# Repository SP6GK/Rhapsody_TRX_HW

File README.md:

# Rhapsody Project

Rhapsody is an ongoing project focused on the development of a modular amateur radio transceiver. The current version of the project features the zero-IF board, which utilizes two balanced Tayloe mixers to convert 1-30 MHz RF signals into baseband IQ that can be processed by an ADC, and to convert baseband IQ generated by a DAC into output RF, implementing a simplex HF transceiver.

In this repository, you can find the first module developed for the Rhapsody project - the IQ board. This PCB implements two balanced Tayloe mixers (or product detectors if you prefer) to implement both transmit and receive paths for an SDR transceiver. Together with a microcontroller and ADC+DAC (or a PC with a sound card), you can create a working HF software-defined transceiver. Special care was put into the design to provide the best IQ balance for superb opposite sideband attenuation.

I have presented more measurements and theory of operation on my personal website: [Description of Rhapsody project on SP6GK.com](https://www.sp6gk.com/Rhapsody_IQ_Board.html). Bare in mind that these results were possible thanks to low tolerance components in the feedback loops of the op amps and software tuning.

The current version of the IQ board is designed for testability. Zero Ohm resistors are implemented as jumpers so that different configurations of RF transformers can be tested. If the value of a resistor is not provided, it is most likely not to be populated (DNP). On the other hand, the zero-Ohm resistors indicate the default option.
RF transformers were wound on FT37-43.

The above results were obtained with my software running on an STM32F407 with a 24-bit 48 KHz ADC/DAC on the I2S interface. [Link to software repository](https://github.com/SP6GK/Rhapsody_TRX_SW)

**Experimental features include:**
- Option to include an additional active LPF in the IQ signal path before the ADC (better spurious image rejection and better anti-aliasing, but may cause worse IQ imbalance; not tested yet)
- Additional passive RC LPF before the RX op amps
- 2.5V reference created by impedance buffer - higher current output for the 2.5V rail should provide even better stability
- External oscillator can be used with a single-ended input. A Johnson Counter then creates an IQ LO. This solution limits the operating frequency to 1/4 of the maximum frequency of the 74xx74 chip used. The onboard PLL can provide an LO signal up to 100 MHz, and its reference is a TCXO or a simple crystal.

**How does it work?**
I recommend the following resources if you want to understand more about the hardware behind this project:
- **Best place to learn about the Tayloe mixer** by Dan Tayloe, [Ultra Low Noise, High Performance, Zero IF Quadrature Product Detector and Preamplifier](https://norcalqrp.org/files/Tayloe_mixer_x3a.pdf)
- **Further description of SDR** by Gerald Youngblood, [A Software-Defined Radio for the Masses](https://www.arrl.org/files/file/Technology/tis/info/pdf/020708qex013.pdf)

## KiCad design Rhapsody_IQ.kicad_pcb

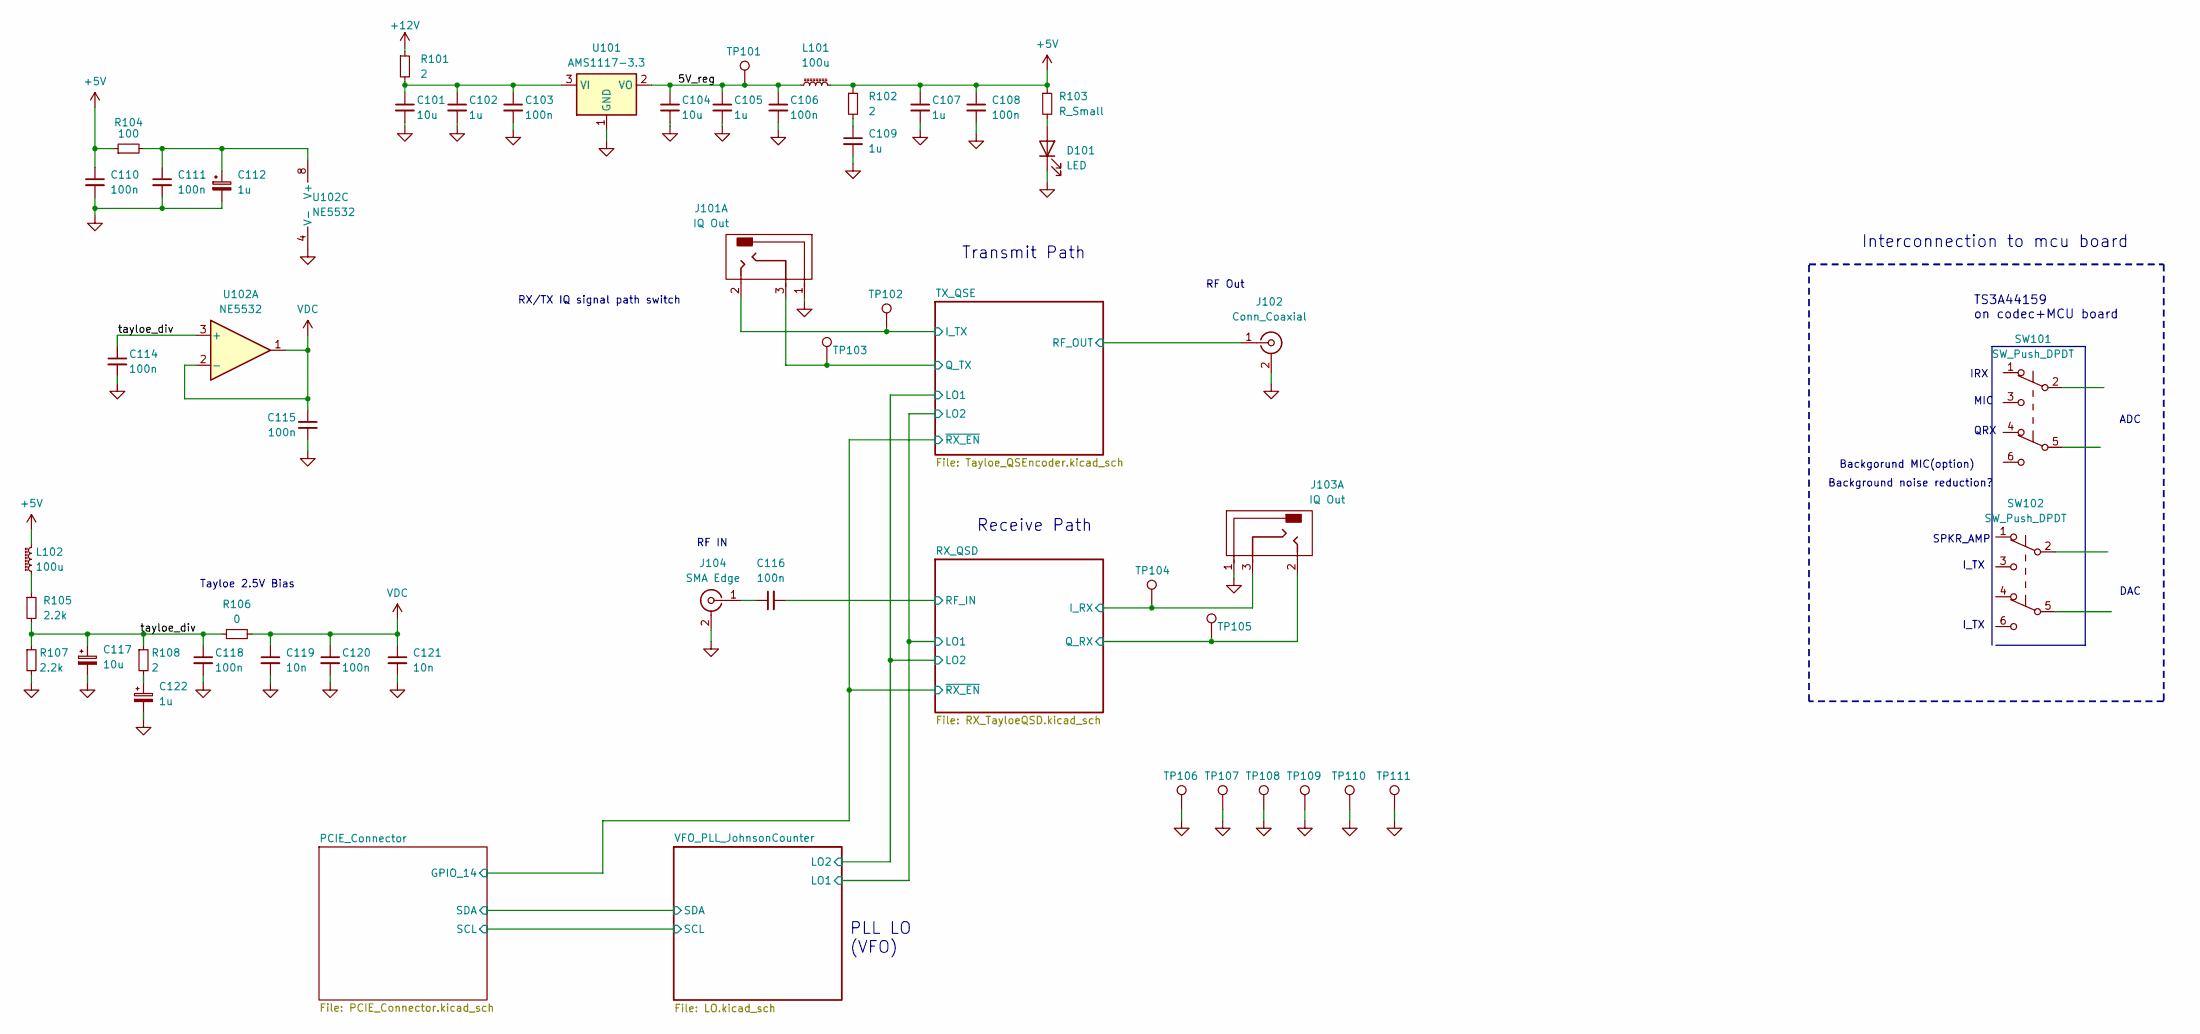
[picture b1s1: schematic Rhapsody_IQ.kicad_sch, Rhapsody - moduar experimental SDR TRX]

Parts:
C101, C104, C117: 10u; C_1206_3216Metric_Pad1.33x1.80mm_HandSolder
C102, C105, C107, C109, C112, C122: 1u; C_0603_1608Metric_Pad1.08x0.95mm_HandSolder
C103, C106, C108, C110, C111, C114, C115, C116, C118, C120: 100n; C_0603_1608Metric_Pad1.08x0.95mm_HandSolder
C119, C121: 10n; C_0603_1608Metric_Pad1.08x0.95mm_HandSolder
D101: LED; D_0805_2012Metric_Pad1.15x1.40mm_HandSolder
J101, J103: IQ Out; Jack_3.5mm_CUI_SJ-3524-SMT_Horizontal
J102: Conn_Coaxial; SMA_Amphenol_132289_EdgeMount
J104: SMA Edge; SMA_Amphenol_132289_EdgeMount
L101, L102: 100u; L_1206_3216Metric_Pad1.22x1.90mm_HandSolder
R101: 2; R_0805_2012Metric_Pad1.20x1.40mm_HandSolder
R102, R108: 2; R_0603_1608Metric_Pad0.98x0.95mm_HandSolder
R103: R_Small; R_0805_2012Metric_Pad1.20x1.40mm_HandSolder
R104: 100; R_0603_1608Metric_Pad0.98x0.95mm_HandSolder
R105, R107: 2.2k; R_0603_1608Metric_Pad0.98x0.95mm_HandSolder
R106: 0; R_0805_2012Metric_Pad1.20x1.40mm_HandSolder
SW101, SW102: SW_Push_DPDT
TP101, TP102, TP103, TP104, TP105, TP106, TP107, TP108, TP109: TestPoint; TestPoint_Pad_D1.5mm
TP110, TP111: TestPoint; TestPoint_Pad_4.0x4.0mm
U101: AMS1117-3.3; SOT-223-3_TabPin2
U102: NE5532; SOIC-8_3.9x4.9mm_P1.27mm

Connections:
+5V: C107.1, C108.1, C110.1, L101.2, L102.2, R102.1, R103.1, R104.1; also elsewhere on the board
+12V: R101.1; also elsewhere on the board
/5V_reg: C104.1, C105.1, C106.1, L101.1, TP101.1, U101.2 (VO)
/RX_QSD/I_RX: J103.3, TP104.1; also elsewhere on the board
/RX_QSD/Q_RX: J103.2, TP105.1; also elsewhere on the board
/RX_QSD/RF_IN: C116.2; also elsewhere on the board
/TX_QSE/I_TX: J101.2, TP102.1; also elsewhere on the board
/TX_QSE/Q_TX: J101.3, TP103.1; also elsewhere on the board
/TX_QSE/RF_OUT: J102.1 (In); also elsewhere on the board
/tayloe_div: C114.1, C117.1, C118.1, R105.2, R106.1, R107.1, R108.1, U102.3 (+)
GND: C101.2, C102.2, C103.2, C104.2, C105.2, C106.2, C107.2, C108.2, C109.2, C110.2, C111.2, C112.2, C114.2, C115.2, C117.2, C118.2, C119.2, C120.2, C121.2, C122.2, D101.1 (K), J101.1, J102.2 (Ext), J103.1, J104.2 (Ext), R107.2, TP106.1, TP107.1, TP108.1, TP109.1, TP110.1, TP111.1, U101.1 (GND), U102.4 (V-); also elsewhere on the board
unnamed: C109.1, R102.2
unnamed: C122.1, R108.2
unnamed: D101.2 (A), R103.2
unnamed: C116.1, J104.1 (In)
unnamed: L102.1, R105.1
unnamed: C101.1, C102.1, C103.1, R101.2, U101.3 (VI)
unnamed: C111.1, C112.1, R104.2, U102.8 (V+)
VDC: C115.1, C119.1, C120.1, C121.1, R106.2, U102.1, U102.2 (-); also elsewhere on the board

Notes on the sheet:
RF IN
DAC
Interconnection to mcu board
Backgorund MIC(option)
RF Out
RX/TX IQ signal path switch
Receive Path
Background noise reduction?
I_TX
SPKR_AMP
ADC
PLL LO (VFO)
TS3A44159 on codec+MCU board
IRX
Transmit Path
Tayloe 2.5V Bias
MIC
QRX

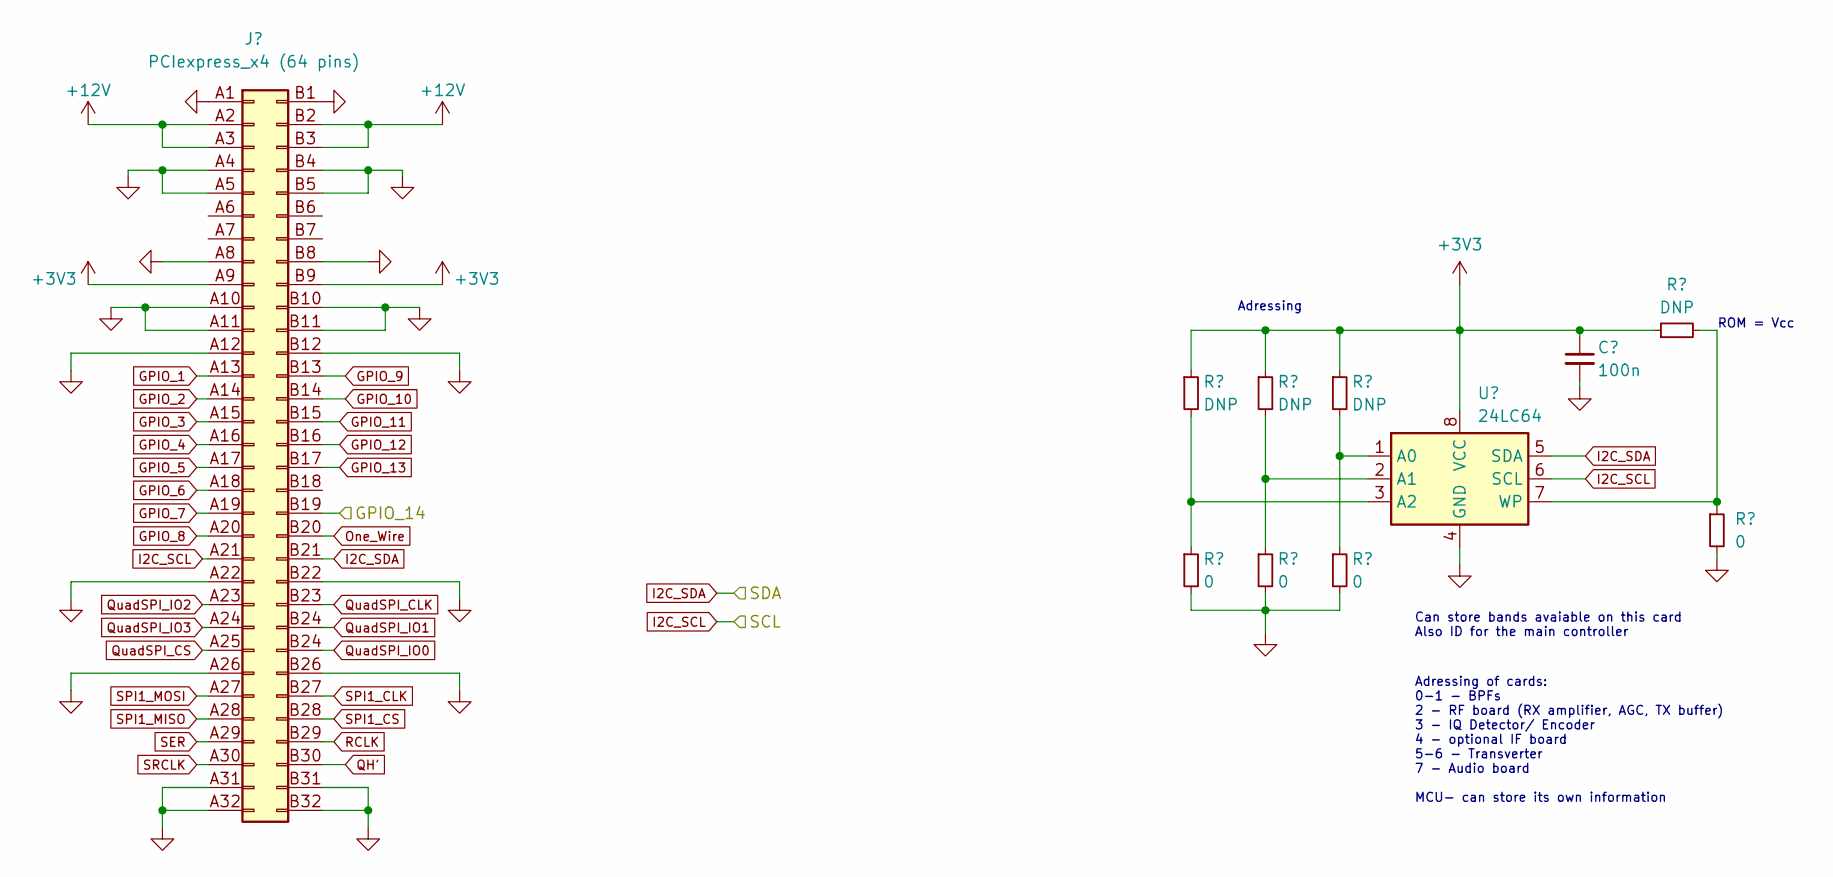
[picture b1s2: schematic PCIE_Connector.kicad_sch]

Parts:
C501: 100n; C_0603_1608Metric_Pad1.08x0.95mm_HandSolder
J501: PCIexpress_x4 (64 pins); BUS_PCIexpress_x4
R501, R502, R503, R504: DNP; R_0805_2012Metric_Pad1.20x1.40mm_HandSolder
R505, R506, R507, R508: 0; R_0805_2012Metric_Pad1.20x1.40mm_HandSolder
U501: 24LC64; SOIC-8_3.9x4.9mm_P1.27mm

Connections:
+3V3: C501.1, J501.A9 (Pin_9), J501.B9 (Pin_56), R501.1, R502.1, R503.1, R504.1, U501.8 (VCC); also elsewhere on the board
+12V: J501.A2 (Pin_2), J501.A3 (Pin_3), J501.B2 (Pin_63), J501.B3 (Pin_62); also elsewhere on the board
/PCIE_Connector/GPIO_14: J501.B19 (Pin_46); also elsewhere on the board
GND: C501.2, J501.A1 (Pin_1), J501.A4 (Pin_4), J501.A5 (Pin_5), J501.A8 (Pin_8), J501.A10 (Pin_10), J501.A11 (Pin_11), J501.A12 (Pin_12), J501.A22 (Pin_22), J501.A26 (Pin_26), J501.A31 (Pin_31), J501.A32 (Pin_32), J501.B1 (Pin_64), J501.B4 (Pin_61), J501.B5 (Pin_60), J501.B8 (Pin_57), J501.B10 (Pin_55), J501.B11 (Pin_54), J501.B12 (Pin_53), J501.B22 (Pin_43), J501.B26 (Pin_39), J501.B31 (Pin_31), J501.B32 (Pin_33), R505.2, R506.2, R507.2, R508.2, U501.4 (GND); also elsewhere on the board
GPIO_1: J501.A13 (Pin_13)
GPIO_2: J501.A14 (Pin_14)
GPIO_3: J501.A15 (Pin_15)
GPIO_4: J501.A16 (Pin_16)
GPIO_5: J501.A17 (Pin_17)
GPIO_6: J501.A18 (Pin_18)
GPIO_7: J501.A19 (Pin_19)
GPIO_8: J501.A20 (Pin_20)
GPIO_9: J501.B13 (Pin_52)
GPIO_10: J501.B14 (Pin_51)
GPIO_11: J501.B15 (Pin_50)
GPIO_12: J501.B16 (Pin_49)
GPIO_13: J501.B17 (Pin_48)
I2C_SCL: J501.A21 (Pin_21), U501.6 (SCL); also elsewhere on the board
unnamed: R504.2, R508.1, U501.1 (A0)
unnamed: R503.2, R507.1, U501.2 (A1)
unnamed: R502.2, R506.1, U501.3 (A2)
unnamed: R501.2, R505.1, U501.7 (WP)
One_Wire: J501.B20 (Pin_45)
QH': J501.B30 (Pin_35)
QuadSPI_CLK: J501.B23 (Pin_42)
QuadSPI_CS: J501.A25 (Pin_25)
QuadSPI_IO2: J501.A23 (Pin_23)
QuadSPI_IO3: J501.A24 (Pin_24)
RCLK: J501.B29 (Pin_36)
SER: J501.A29 (Pin_29)
SPI1_CLK: J501.B27 (Pin_38)
SPI1_CS: J501.B28 (Pin_37)
SPI1_MISO: J501.A28 (Pin_28)
SPI1_MOSI: J501.A27 (Pin_27)
SRCLK: J501.A30 (Pin_30)

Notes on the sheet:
Adressing
Can store bands avaiable on this card Also ID for the main controller
Adressing of cards: 0-1 - BPFs 2 - RF board (RX amplifier, AGC, TX buffer) 3 - IQ Detector/ Encoder 4 - optional IF board 5-6 - Transverter 7 - Audio board MCU- can store its own information
ROM = Vcc

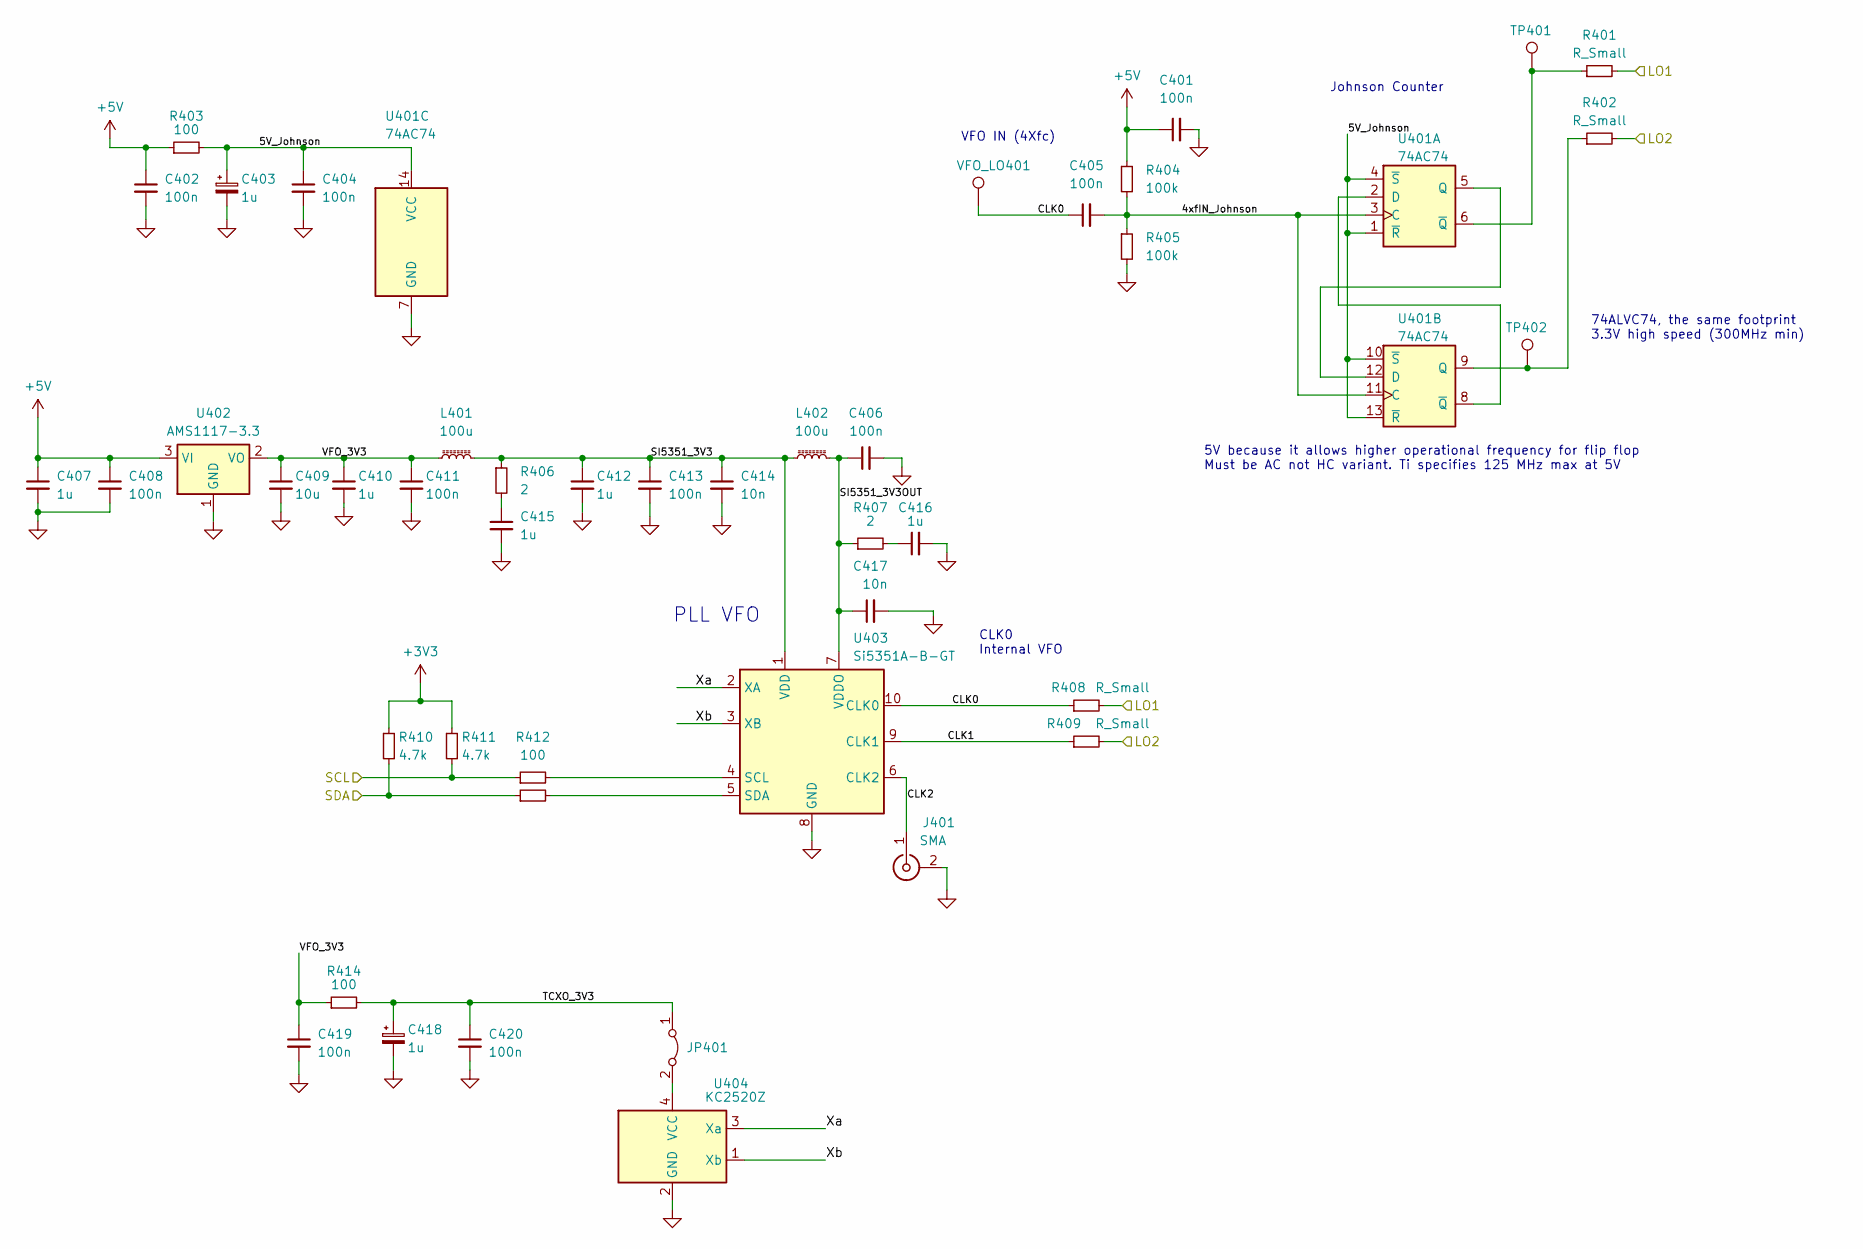
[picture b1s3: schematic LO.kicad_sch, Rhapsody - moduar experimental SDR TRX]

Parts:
C401, C402, C404, C405, C406, C408, C411, C413, C419, C420: 100n; C_0603_1608Metric_Pad1.08x0.95mm_HandSolder
C403, C407, C410, C412, C415, C416, C418: 1u; C_0603_1608Metric_Pad1.08x0.95mm_HandSolder
C409: 10u; C_1206_3216Metric_Pad1.33x1.80mm_HandSolder
C414, C417: 10n; C_0603_1608Metric_Pad1.08x0.95mm_HandSolder
J401: SMA; SMA_Wurth_60312102114405_Vertical
JP401: Jumper_2_Bridged; SolderJumper-2_P1.3mm_Open_Pad1.0x1.5mm
L401: 100u; L_1206_3216Metric_Pad1.22x1.90mm_HandSolder
L402: 100u; L_0805_2012Metric_Pad1.05x1.20mm_HandSolder
R401, R402, R408, R409: R_Small; R_1206_3216Metric_Pad1.30x1.75mm_HandSolder
R403, R412, R414: 100; R_0603_1608Metric_Pad0.98x0.95mm_HandSolder
R404, R405: 100k; R_0603_1608Metric_Pad0.98x0.95mm_HandSolder
R406, R407: 2; R_0603_1608Metric_Pad0.98x0.95mm_HandSolder
R410, R411: 4.7k; R_0603_1608Metric_Pad0.98x0.95mm_HandSolder
R413: R_Small; R_0603_1608Metric_Pad0.98x0.95mm_HandSolder
TP401, TP402: TestPoint; TestPoint_Pad_D1.5mm
U401: 74AC74; SO-14_3.9x8.65mm_P1.27mm
U402: AMS1117-3.3; SOT-223-3_TabPin2
U403: Si5351A-B-GT; MSOP-10_3x3mm_P0.5mm
U404: KC2520Z; Crystal_SMD_3225-4Pin_3.2x2.5mm_HandSoldering
VFO_LO401: TestPoint; TestPoint_Pad_D1.5mm

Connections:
+3V3: R410.1, R411.1; also elsewhere on the board
+5V: C401.1, C402.1, C407.1, C408.1, R403.1, R404.1, U402.3 (VI); also elsewhere on the board
/VFO_PLL_JohnsonCounter/4xfIN_Johnson: C405.2, R404.2, R405.1, U401.3 (C), U401.11 (C)
/VFO_PLL_JohnsonCounter/5V_Johnson: C403.1, C404.1, R403.2, U401.1 (~R), U401.4 (~S), U401.10 (~S), U401.13 (~R), U401.14 (VCC)
/VFO_PLL_JohnsonCounter/CLK2: J401.1 (In), U403.6 (CLK2)
/VFO_PLL_JohnsonCounter/SI5351_3V3: C412.1, C413.1, C414.1, L401.2, L402.1, R406.1, U403.1 (VDD)
/VFO_PLL_JohnsonCounter/SI5351_3V3OUT: C406.1, C417.1, L402.2, R407.1, U403.7 (VDDO)
/VFO_PLL_JohnsonCounter/Xa: U403.2 (XA), U404.3 (Xa)
/VFO_PLL_JohnsonCounter/Xb: U403.3 (XB), U404.1 (Xb)
GND: C401.2, C402.2, C403.2, C404.2, C406.2, C407.2, C408.2, C409.2, C410.2, C411.2, C412.2, C413.2, C414.2, C415.2, C416.2, C417.2, C418.2, C419.2, C420.2, J401.2 (Ext), R405.2, U401.7 (GND), U402.1 (GND), U403.8 (GND), U404.2 (GND); also elsewhere on the board
I2C_SCL: R411.2, R412.1; also elsewhere on the board
unnamed: C415.1, R406.2
unnamed: C416.1, R407.2
unnamed: JP401.2 (B), U404.4 (VCC)
unnamed: U401.2 (D), U401.8 (~Q)
unnamed: U401.5 (Q), U401.12 (D)
unnamed: R401.1, TP401.1, U401.6 (~Q)
unnamed: R402.1, TP402.1, U401.9 (Q)
unnamed: R412.2, U403.4 (SCL)

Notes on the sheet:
CLK0 Internal VFO
VFO IN (4Xfc)
PLL VFO
Johnson Counter
74ALVC74, the same footprint 3.3V high speed (300MHz min)
5V because it allows higher operational frequency for flip flop Must be AC not HC variant. Ti specifies 125 MHz max at 5V

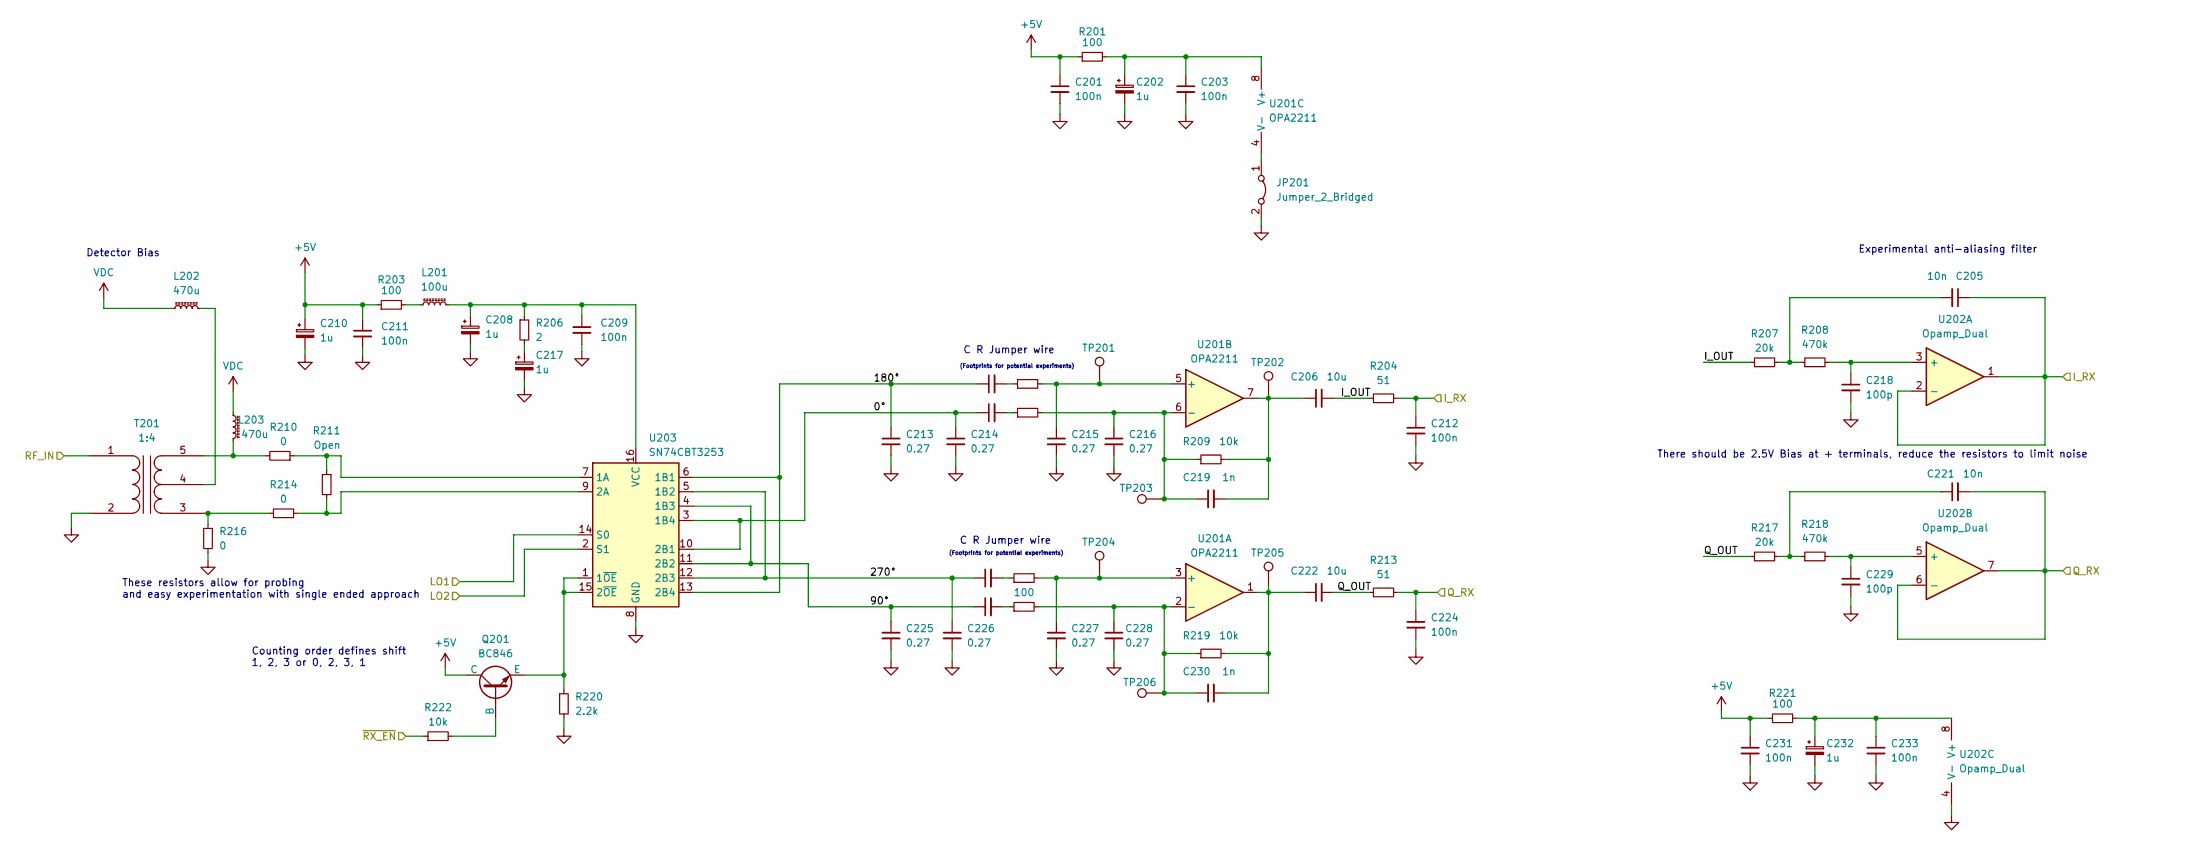
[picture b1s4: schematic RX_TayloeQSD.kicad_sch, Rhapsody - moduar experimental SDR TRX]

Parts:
C201, C203, C209, C211, C231, C233: 100n; C_0603_1608Metric_Pad1.08x0.95mm_HandSolder
C202, C208, C210, C217, C232: 1u; C_0603_1608Metric_Pad1.08x0.95mm_HandSolder
C204, C206, C207, C220, C222, C223: 10u; C_1206_3216Metric_Pad1.33x1.80mm_HandSolder
C205, C221: 10n; C_0805_2012Metric_Pad1.18x1.45mm_HandSolder
C212, C224: 100n; C_1206_3216Metric_Pad1.33x1.80mm_HandSolder
C213, C214, C215, C216, C225, C226, C227, C228: 0.27; C_1206_3216Metric_Pad1.33x1.80mm_HandSolder
C218, C229: 100p; C_0805_2012Metric_Pad1.18x1.45mm_HandSolder
C219, C230: 1n; C_0805_2012Metric_Pad1.18x1.45mm_HandSolder
JP201: Jumper_2_Bridged; R_0805_2012Metric_Pad1.20x1.40mm_HandSolder
L201: 100u; L_1206_3216Metric_Pad1.22x1.90mm_HandSolder
L202, L203: 470u; L_1206_3216Metric_Pad1.22x1.90mm_HandSolder
Q201: BC846; SOT-23-3
R201, R203, R221: 100; R_0603_1608Metric_Pad0.98x0.95mm_HandSolder
R202, R205, R215: 200; R_1206_3216Metric_Pad1.30x1.75mm_HandSolder
R204, R213: 51; R_1206_3216Metric_Pad1.30x1.75mm_HandSolder
R206: 2; R_0603_1608Metric_Pad0.98x0.95mm_HandSolder
R207, R217: 20k; R_0805_2012Metric_Pad1.20x1.40mm_HandSolder
R208, R218: 470k; R_0805_2012Metric_Pad1.20x1.40mm_HandSolder
R209, R219: 10k; R_1206_3216Metric_Pad1.30x1.75mm_HandSolder
R210, R214, R216: 0; R_1206_3216Metric_Pad1.30x1.75mm_HandSolder
R211: Open; R_1206_3216Metric_Pad1.30x1.75mm_HandSolder
R212: 100; R_1206_3216Metric_Pad1.30x1.75mm_HandSolder
R220: 2.2k; R_0603_1608Metric_Pad0.98x0.95mm_HandSolder
R222: 10k; R_0603_1608Metric_Pad0.98x0.95mm_HandSolder
T201: 1:4; T37_toroid
TP201, TP202, TP203, TP204, TP205, TP206: TestPoint; TestPoint_Pad_D1.5mm
U201: OPA2211; SOIC-8_3.9x4.9mm_P1.27mm
U202: Opamp_Dual; SOIC-8_3.9x4.9mm_P1.27mm
U203: SN74CBT3253; SOIC-16_4.55x10.3mm_P1.27mm

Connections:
+5V: C201.1, C210.1, C211.1, C231.1, Q201.3 (C), R201.1, R203.1, R221.1; also elsewhere on the board
/PCIE_Connector/GPIO_14: R222.1; also elsewhere on the board
/RX_QSD/0°: C207.1, C214.1, U203.3 (1B4), U203.10 (2B1)
/RX_QSD/90°: C223.1, C225.1, U203.4 (1B3), U203.11 (2B2)
/RX_QSD/180°: C204.1, C213.1, U203.6 (1B1), U203.13 (2B4)
/RX_QSD/270°: C220.1, C226.1, U203.5 (1B2), U203.12 (2B3)
/RX_QSD/I_OUT: C206.2, R204.1, R207.1
/RX_QSD/I_RX: C205.1, C212.1, R204.2, U202.1, U202.2 (-); also elsewhere on the board
/RX_QSD/Q_OUT: C222.2, R213.1, R217.1
/RX_QSD/Q_RX: C221.2, C224.1, R213.2, U202.6 (-), U202.7; also elsewhere on the board
/RX_QSD/RF_IN: T201.1 (AA); also elsewhere on the board
GND: C201.2, C202.2, C203.2, C208.2, C209.2, C210.2, C211.2, C212.2, C213.2, C214.2, C215.2, C216.2, C217.2, C218.2, C224.2, C225.2, C226.2, C227.2, C228.2, C229.2, C231.2, C232.2, C233.2, JP201.2 (B), R216.2, R220.2, T201.2 (AB), U202.4 (V-), U203.8 (GND); also elsewhere on the board
unnamed: C204.2, R202.1
unnamed: C205.2, R207.2, R208.1
unnamed: C206.1, C219.2, R209.2, TP202.1, U201.7
unnamed: C207.2, R205.1
unnamed: C217.1, R206.2
unnamed: C220.2, R212.1
unnamed: C221.1, R217.2, R218.1
unnamed: C222.1, C230.2, R219.2, TP205.1, U201.1
unnamed: C223.2, R215.1
unnamed: JP201.1 (A), U201.4 (V-)
unnamed: L201.1, R203.2
unnamed: Q201.1 (B), R222.2
unnamed: Q201.2 (E), R220.1, U203.1 (1~OE), U203.15 (2~OE)
unnamed: R214.2, R216.1, T201.3 (SA)
unnamed: L203.2, R210.2, T201.5 (SB)
unnamed: L202.2, T201.4 (SC)
unnamed: C227.1, R212.2, TP204.1, U201.3 (+)
unnamed: C228.1, C230.1, R215.2, R219.1, TP206.1, U201.2 (-)
unnamed: C215.1, R202.2, TP201.1, U201.5 (+)
unnamed: C216.1, C219.1, R205.2, R209.1, TP203.1, U201.6 (-)
unnamed: C202.1, C203.1, R201.2, U201.8 (V+)
unnamed: C218.1, R208.2, U202.3 (+)
unnamed: C229.1, R218.2, U202.5 (+)
unnamed: C232.1, C233.1, R221.2, U202.8 (V+)
unnamed: R210.1, R211.1, U203.7 (1A)
unnamed: R211.2, R214.1, U203.9 (2A)
unnamed: C208.1, C209.1, L201.2, R206.1, U203.16 (VCC)
VDC: L202.1, L203.1; also elsewhere on the board

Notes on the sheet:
Counting order defines shift 1, 2, 3 or 0, 2, 3, 1
There should be 2.5V Bias at + terminals, reduce the resistors to limit noise
These resistors allow for probing and easy experimentation with single ended approach
Detector Bias
Experimental anti-aliasing filter
C R Jumper wire
(Footprints for potential experiments)

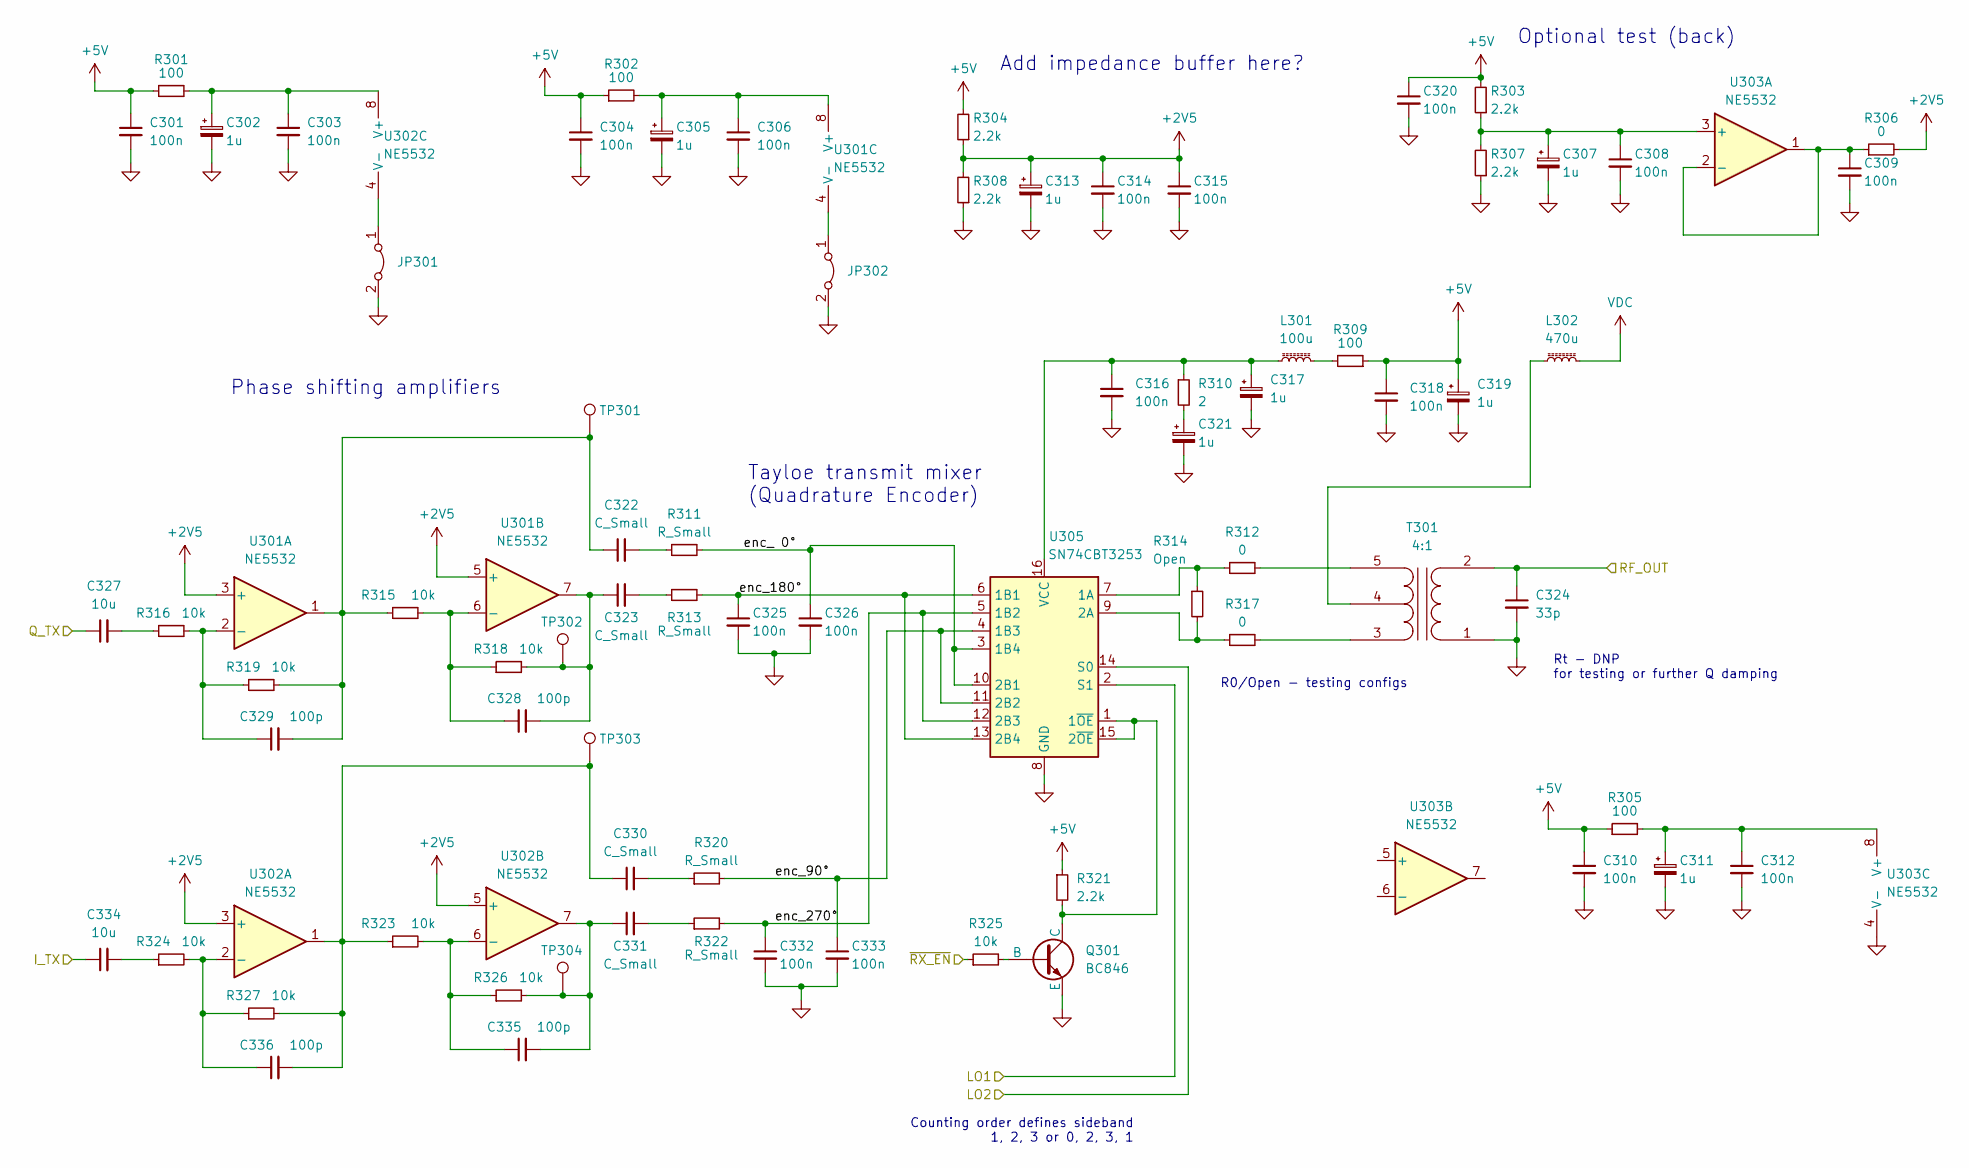
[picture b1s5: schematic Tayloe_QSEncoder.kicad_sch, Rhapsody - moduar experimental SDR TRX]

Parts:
C301, C303, C304, C306, C308, C309, C310, C312, C314, C315, C316, C318, C320: 100n; C_0603_1608Metric_Pad1.08x0.95mm_HandSolder
C302, C305, C307, C311, C313, C317, C319, C321: 1u; C_0603_1608Metric_Pad1.08x0.95mm_HandSolder
C322, C323, C330, C331: C_Small; C_1206_3216Metric_Pad1.33x1.80mm_HandSolder
C324: 33p; C_0805_2012Metric_Pad1.18x1.45mm_HandSolder
C325, C326, C332, C333: 100n; C_1206_3216Metric_Pad1.33x1.80mm_HandSolder
C327, C334: 10u; C_1206_3216Metric_Pad1.33x1.80mm_HandSolder
C328, C329, C335, C336: 100p; C_1206_3216Metric_Pad1.33x1.80mm_HandSolder
JP301, JP302: Jumper_2_Bridged; R_0805_2012Metric_Pad1.20x1.40mm_HandSolder
L301: 100u; L_1206_3216Metric_Pad1.22x1.90mm_HandSolder
L302: 470u; L_1206_3216Metric_Pad1.22x1.90mm_HandSolder
Q301: BC846; SOT-23-3
R301, R305, R309: 100; R_0603_1608Metric_Pad0.98x0.95mm_HandSolder
R302: 100; R_0805_2012Metric_Pad1.20x1.40mm_HandSolder
R303, R304, R307, R308, R321: 2.2k; R_0603_1608Metric_Pad0.98x0.95mm_HandSolder
R306, R312, R317: 0; R_1206_3216Metric_Pad1.30x1.75mm_HandSolder
R310: 2; R_0603_1608Metric_Pad0.98x0.95mm_HandSolder
R311, R313, R320, R322: R_Small; R_1206_3216Metric_Pad1.30x1.75mm_HandSolder
R314: Open; R_1206_3216Metric_Pad1.30x1.75mm_HandSolder
R315: 10k; R_1206_3216Metric
R316, R323, R324, R326, R327: 10k; R_1206_3216Metric_Pad1.30x1.75mm_HandSolder
R318, R319: 10k; C_1206_3216Metric_Pad1.33x1.80mm_HandSolder
R325: 10k; R_0603_1608Metric_Pad0.98x0.95mm_HandSolder
T301: 4:1; T37_toroid
TP301, TP302, TP303, TP304: TestPoint; TestPoint_Pad_D1.5mm
U301, U302, U303: NE5532; SOIC-8_3.9x4.9mm_P1.27mm
U305: SN74CBT3253; SOIC-16_4.55x10.3mm_P1.27mm

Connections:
+2V5: C313.1, C314.1, C315.1, R304.1, R306.2, R308.2, U301.3 (+), U301.5 (+), U302.3 (+), U302.5 (+)
+5V: C301.1, C304.1, C310.1, C318.1, C319.1, C320.1, R301.1, R302.1, R303.2, R304.2, R305.1, R309.1, R321.1; also elsewhere on the board
/PCIE_Connector/GPIO_14: R325.1; also elsewhere on the board
/TX_QSE/I_TX: C334.1; also elsewhere on the board
/TX_QSE/Q_TX: C327.1; also elsewhere on the board
/TX_QSE/RF_OUT: C324.1, T301.2 (AA); also elsewhere on the board
/TX_QSE/enc_90°: C333.1, R320.2, U305.4 (1B3), U305.11 (2B2)
/TX_QSE/enc_180°: C325.1, R313.2, U305.6 (1B1), U305.13 (2B4)
/TX_QSE/enc_270°: C332.1, R322.2, U305.5 (1B2), U305.12 (2B3)
/TX_QSE/enc_ 0°: C326.1, R311.2, U305.3 (1B4), U305.10 (2B1)
GND: C301.2, C302.2, C303.2, C304.2, C305.2, C306.2, C307.2, C308.2, C309.2, C310.2, C311.2, C312.2, C313.2, C314.2, C315.2, C316.2, C317.2, C318.2, C319.2, C320.2, C321.2, C324.2, C325.2, C326.2, C332.2, C333.2, JP301.2 (B), JP302.2 (B), Q301.2 (E), R307.1, R308.1, T301.1 (AB), U303.4 (V-), U305.8 (GND); also elsewhere on the board
unnamed: C321.1, R310.2
unnamed: C322.1, C329.2, R315.1, R319.2, TP301.1, U301.1
unnamed: C322.2, R311.1
unnamed: C323.1, C328.2, R318.2, TP302.1, U301.7
unnamed: C323.2, R313.1
unnamed: C327.2, R316.1
unnamed: C330.1, C336.2, R323.1, R327.2, TP303.1, U302.1
unnamed: C330.2, R320.1
unnamed: C331.1, C335.2, R326.2, TP304.1, U302.7
unnamed: C331.2, R322.1
unnamed: C334.2, R324.1
unnamed: JP301.1 (A), U302.4 (V-)
unnamed: JP302.1 (A), U301.4 (V-)
unnamed: L301.1, R309.2
unnamed: Q301.1 (B), R325.2
unnamed: Q301.3 (C), R321.2, U305.1 (1~OE), U305.15 (2~OE)
unnamed: R317.2, T301.3 (SA)
unnamed: R312.2, T301.5 (SB)
unnamed: L302.2, T301.4 (SC)
unnamed: C329.1, R316.2, R319.1, U301.2 (-)
unnamed: C328.1, R315.2, R318.1, U301.6 (-)
unnamed: C305.1, C306.1, R302.2, U301.8 (V+)
unnamed: C336.1, R324.2, R327.1, U302.2 (-)
unnamed: C335.1, R323.2, R326.1, U302.6 (-)
unnamed: C302.1, C303.1, R301.2, U302.8 (V+)
unnamed: C307.1, C308.1, R303.1, R307.2, U303.3 (+)
unnamed: C309.1, R306.1, U303.1, U303.2 (-)
unnamed: C311.1, C312.1, R305.2, U303.8 (V+)
unnamed: R312.1, R314.1, U305.7 (1A)
unnamed: R314.2, R317.1, U305.9 (2A)
unnamed: C316.1, C317.1, L301.2, R310.1, U305.16 (VCC)
VDC: L302.1; also elsewhere on the board

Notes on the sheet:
R0/Open - testing configs
Add impedance buffer here?
Optional test (back)
Rt - DNP for testing or further Q damping
Phase shifting amplifiers
Tayloe transmit mixer (Quadrature Encoder)
Counting order defines sideband 1, 2, 3 or 0, 2, 3, 1

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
